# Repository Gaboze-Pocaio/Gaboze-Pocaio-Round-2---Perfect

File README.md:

-----

# Where Can I Buy One
> You can purchase an assembled Gaboze Pocaio - Round 2 on [Tindie](https://www.tindie.com/products/thirtytwoteeth/gaboze-pocaio-round-2/)

-----

# 
> This is it!

Based on the popularity of the original [Gaboze Pocaio](https://github.com/32teeth/GabozePocaio-Round1) and it's many updates. We have taken the *Gaboze Pocaio - Plus Edition* which featured the 2.6" TFT *(ILI9342)* and added a few more features

Project Code Name: ***'Play It Again'***

## Introduction
> Do we need one?

### Features
> Things you can find on this kit

- 2.6" TFT LCD
- USB peripheral support for *3.3v accessories* (ie: keyboards)
- Brightness Control Thumbwheel
- Volume Control Thumbwheel
- Power LED - 3mm diffused
- New Conductive Pads
- Through Hole Raspberry Pi Zero Mounting Header
- Battery Charger (TP4056 Module)
- Headphone Jack (LM4857)
- Speaker capability (LM4857)
- Audio Amp (LM4857)

| Top Side Features | Bottom Side Features |
| - | - |
|  |  |

### Platform Support:

- [x] [Emulation Station](http://www.emulationstation.org/)
- [x] [Lakka](http://www.lakka.tv/)
- [x] [RetroPie](https://retropie.org.uk/)

*For [Lakka](http://www.lakka.tv/) implementation you can follow the ['paint by numbers' tutorial](https://github.com/32teeth/Lakka-For-Gaboze-Pocaio)*

#### New Feature Discussion
> A little more behind the features

##### TFT
> A new screen

An adoption from the *Gaboze Pocaio - Plus Edition*. The screen is now a 2.6" TFT, which fills the screen area of the Game Boy Pocket shell much better. No more resizing of the video driver output!

##### Brightness Control
> Mechanical Adjustment FTW

Although there are many implementations of *software* based screen brightness adjustment. This model features a **thubwheel**, which means you don't need to worry about knowing how, or where to put the *software* based controls.

This also allows for using different *Operating Systems* and having brightness control out of the box

##### Through Hole Header
> No more loose connections

With the new Raspberry Pi Zero mounting system using a through hole header, you will no longer loosen the pin connection if using an unregulated (non temperature) control soldering iron...   ...yay

The short insulation on the header also means you can mount the Raspberry Pi flat against the headers

##### New Conductive Pads
> Better response. Simply put

With a redesigned conductive pad, you can now have a better response rate to your silicon aftermarket pads.

##### USB peripheral support
> No connection? No Problem

This is a 3.3V USB peripheral support, like keyboards (not the LED mechanical ones), older joysticks / gamepads *(can you say retro pads!)*

One of the most requested features is to be able to use your keyboard and terminal without having to connect to the network, SSH, SCP, or FTP.

##### Power LED
> Domed and diffused

We replaced the surface mount power indicator LED with a through hole domed and diffused 3mm LED. This fits perfectly in the LED hole of the original and aftermarket *Game Boy Pocket* shell

## What you need
> Batteries not included

In order to complete your build. You will need:

- Raspberry Pi Zero W
- LiPo Battery
- Micro SD Card
- Gameboy Pocket Shell

## Releases
> Retro Pie or Lakka - You Decide

* [Retro Pie](https://github.com/32teeth/GabozePocaio-Round2/releases/tag/RetroPie)
* [Lakka](https://github.com/32teeth/GabozePocaio-Round2/releases/tag/Lakka)

### Direct Downloads

#### Retro Pie
* [IMG](http://gameboy.32teeth.org/Gaboze-Round2-RetroPie.img)
* [GZIP](http://gameboy.32teeth.org/Gaboze-Round2-RetroPie.gz)

#### Lakka
* [IMG](http://gameboy.32teeth.org/Gaboze-Round2-Lakka.img)
* [GZIP](http://gameboy.32teeth.org/Gaboze-Round2-Lakka.gz)

### Get In Touch

|      |
| ---- |
| Find us on the internet and lets chat |

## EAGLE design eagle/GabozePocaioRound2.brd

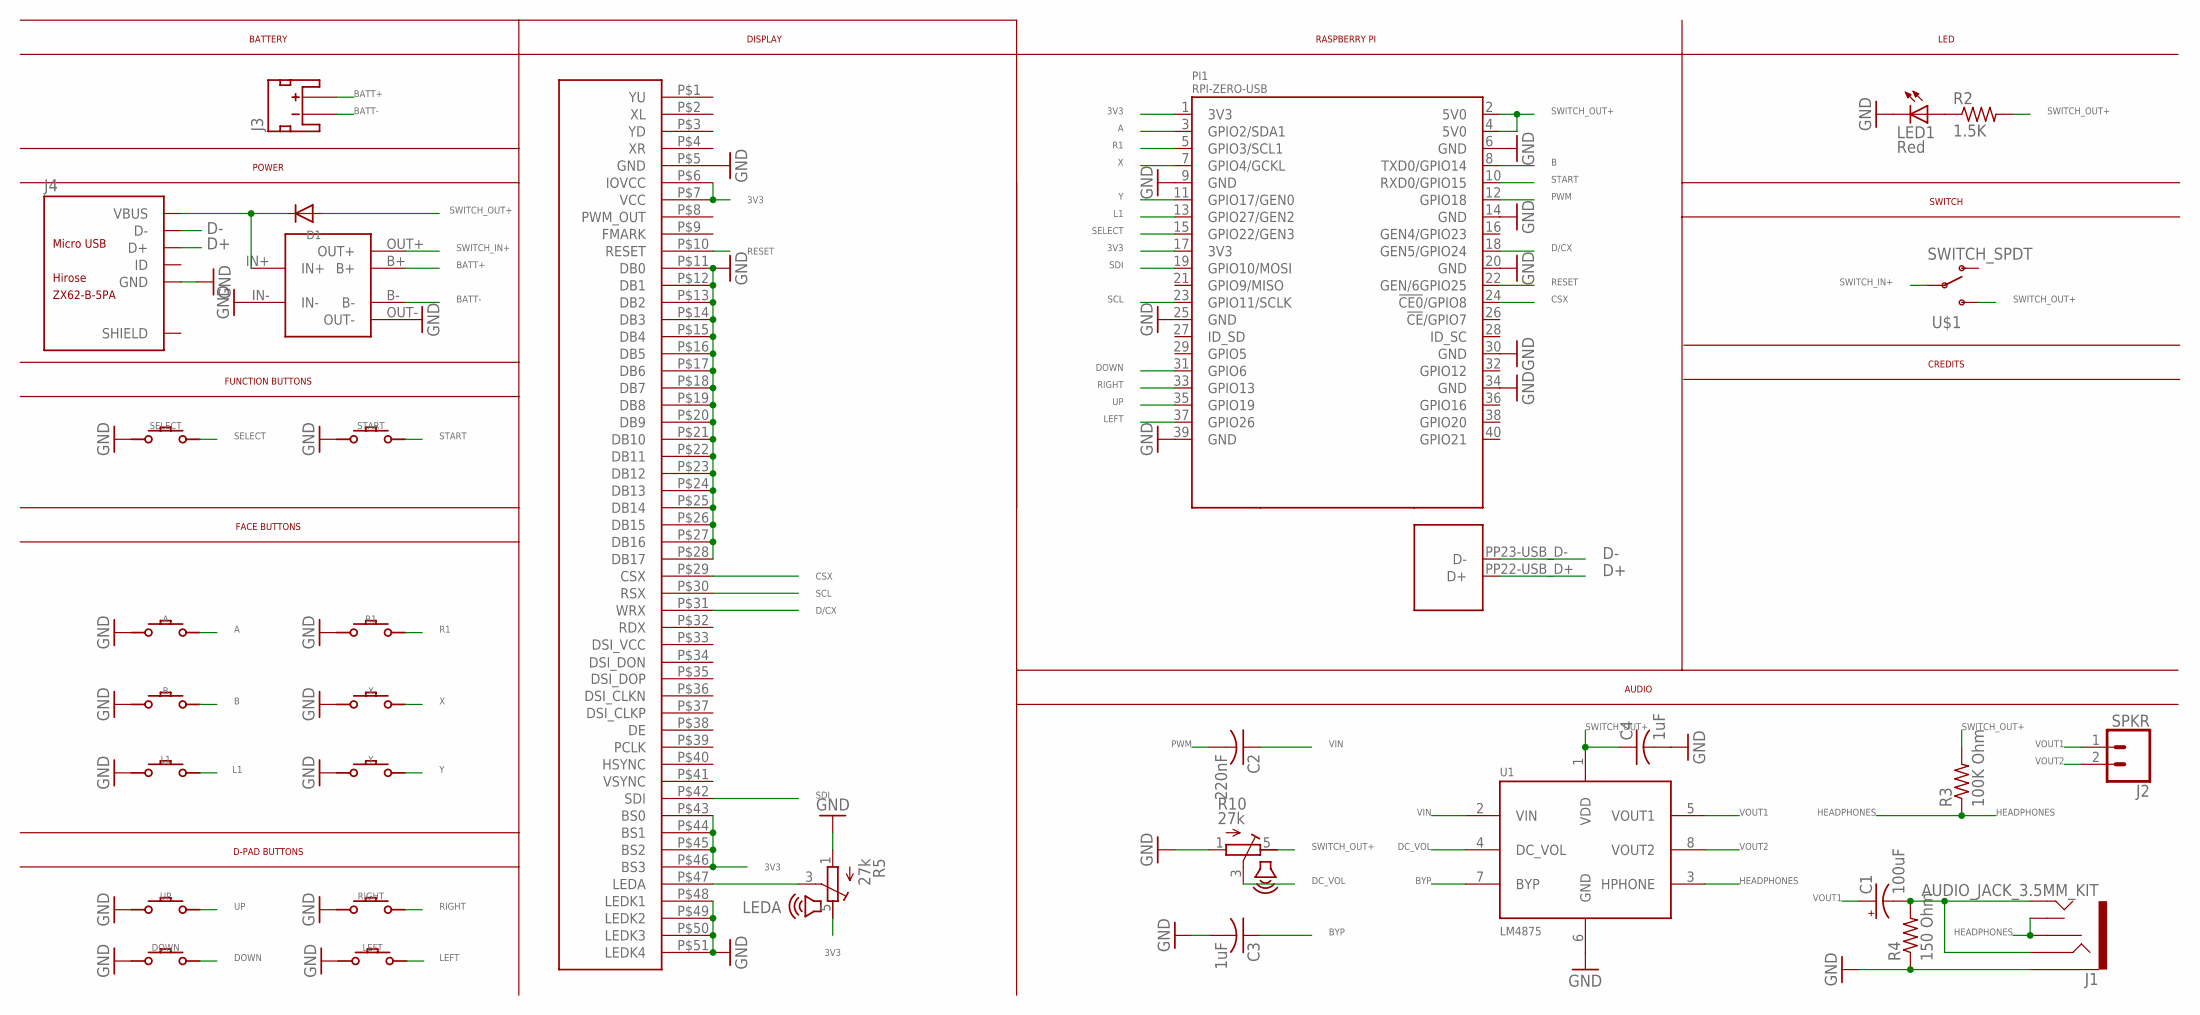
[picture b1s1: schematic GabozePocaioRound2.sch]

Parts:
A: CONDUCTIVE_BUTTONCONDUCTIVE_BUTTON_THICK; CONDUCTIVE_BUTTON_THICK
B: CONDUCTIVE_BUTTONCONDUCTIVE_BUTTON_THICK; CONDUCTIVE_BUTTON_THICK
C1: 100uF; EIA3216
C2: 220nF; C0805
C3, C4: 1uF; C0805
D1: DIODE_SOD-123FL; SOD-123FL
DOWN: CONDUCTIVE_BUTTONCONDUCTIVE_BUTTON_DIRECTIONAL_TH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; CONDUCTIVE_BUTTON_DIRECTIONAL_THICK
J1: AUDIO_JACK_3.5MM_KIT; AUDIO-JACK-KIT
J2: SPKR; 1X02
J3: Batt Conn; JST-2-SMD
J4: ZX62-B-5PA; MICRO-USB5+6P-SMD-0.65-AB
L1: CONDUCTIVE_BUTTON_DRILLCONDUCTIVE_BUTTON_DRILL_TH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; CONDUCTIVE_BUTTON_THICK_DRILL
LED1: Red; LED3MM
LEFT: CONDUCTIVE_BUTTONCONDUCTIVE_BUTTON_DIRECTIONAL_TH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; CONDUCTIVE_BUTTON_DIRECTIONAL_THICK
PI1: RPI-ZERO-USB; RPI-ZERO-TH-USB-POGO
POWER1: TP4056
R1: CONDUCTIVE_BUTTON_DRILLCONDUCTIVE_BUTTON_DRILL_TH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; CONDUCTIVE_BUTTON_THICK_DRILL
R2: 1.5K; R0805
R3: 100K Ohm; R0805
R4: 150 Ohm; R0805
R5, R10: 27k; VOLUME
RIGHT: CONDUCTIVE_BUTTONCONDUCTIVE_BUTTON_DIRECTIONAL_TH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; CONDUCTIVE_BUTTON_DIRECTIONAL_THICK
SELECT: CONDUCTIVE_BUTTON_STARTSELECTCONDUCTIVE_BUTTON_TH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; CONDUCTIVE_BUTTON_THICK_STARTSELECT
START: CONDUCTIVE_BUTTON_STARTSELECTCONDUCTIVE_BUTTON_TH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; CONDUCTIVE_BUTTON_THICK_STARTSELECT
U1: LM4875; SOIC8
U$1: SWITCH_SPDT; KPS-1290
U$2: TFT-DISPLAY-2.6-51PIN
UP: CONDUCTIVE_BUTTONCONDUCTIVE_BUTTON_DIRECTIONAL_TH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; CONDUCTIVE_BUTTON_DIRECTIONAL_THICK
X: CONDUCTIVE_BUTTON_DRILLCONDUCTIVE_BUTTON_DRILL_TH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; CONDUCTIVE_BUTTON_THICK_DRILL
Y: CONDUCTIVE_BUTTON_DRILLCONDUCTIVE_BUTTON_DRILL_TH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; CONDUCTIVE_BUTTON_THICK_DRILL

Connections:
3V3: PI1.1 (3V3), PI1.17 (3V3), R5.5 (E), U$2.P$6 (IOVCC), U$2.P$7 (VCC), U$2.P$43 (BS0), U$2.P$44 (BS1), U$2.P$45 (BS2), U$2.P$46 (BS3)
A: A.P$ACTIVE, PI1.3 (GPIO2/SDA1)
B: B.P$ACTIVE, PI1.8 (TXD0/GPIO14)
BATT+: J3.2 (+), POWER1.B+
BATT-: J3.1 (-), POWER1.B-
BYP: C3.1, U1.7 (BYP)
CSX: PI1.24 (!CE0!/GPIO8), U$2.P$29 (CSX)
D+: J4.3 (D+), PI1.PP22-USB_D+ (D+)
D-: J4.2 (D-), PI1.PP23-USB_D- (D-)
D/CX: PI1.18 (GEN5/GPIO24), U$2.P$31 (WRX)
DC_VOL: R10.3 (S), U1.4 (DC_VOL)
DOWN: DOWN.P$ACTIVE, PI1.31 (GPIO6)
GND: A.P$GND, B.P$GND, C3.2, C4.2, DOWN.P$GND, J1.SLEEVE, J4.5 (GND), L1.P$GND, LED1.K (C), LEFT.P$GND, PI1.6 (GND), PI1.9 (GND), PI1.14 (GND), PI1.20 (GND), PI1.25 (GND), PI1.30 (GND), PI1.34 (GND), PI1.39 (GND), POWER1.IN-, POWER1.OUT-, R1.P$GND, R4.1, R5.1 (A), R10.1 (A), RIGHT.P$GND, SELECT.P$GND, SELECT.P$GND1 (P$GND), SELECT.P$GND2 (P$GND), SELECT.P$GND3 (P$GND), START.P$GND, START.P$GND1 (P$GND), START.P$GND2 (P$GND), START.P$GND3 (P$GND), U1.6 (GND), U$2.P$5 (GND), U$2.P$11 (DB0), U$2.P$12 (DB1), U$2.P$13 (DB2), U$2.P$14 (DB3), U$2.P$15 (DB4), U$2.P$16 (DB5), U$2.P$17 (DB6), U$2.P$18 (DB7), U$2.P$19 (DB8), U$2.P$20 (DB9), U$2.P$21 (DB10), U$2.P$22 (DB11), U$2.P$23 (DB12), U$2.P$24 (DB13), U$2.P$25 (DB14), U$2.P$26 (DB15), U$2.P$27 (DB16), U$2.P$28 (DB17), U$2.P$48 (LEDK1), U$2.P$49 (LEDK2), U$2.P$50 (LEDK3), U$2.P$51 (LEDK4), UP.P$GND, X.P$GND, Y.P$GND
HEADPHONES: J1.RSH, J1.TSH, R3.1, U1.3 (HPHONE)
L1: L1.P$ACTIVE, PI1.13 (GPIO27/GEN2)
LED: LED1.A, R2.1
LEDA: R5.3 (S), U$2.P$47 (LEDA)
LEFT: LEFT.P$ACTIVE, PI1.37 (GPIO26)
PWM: C2.2, PI1.12 (GPIO18)
R1: PI1.5 (GPIO3/SCL1), R1.P$ACTIVE
RESET: PI1.22 (GEN/6GPIO25), U$2.P$10 (RESET)
RIGHT: PI1.33 (GPIO13), RIGHT.P$ACTIVE
SCL: PI1.23 (GPIO11/SCLK), U$2.P$30 (RSX)
SDI: PI1.19 (GPIO10/MOSI), U$2.P$42 (SDI)
SELECT: PI1.15 (GPIO22/GEN3), SELECT.P$ACTIVE, SELECT.P$ACTIVE1 (P$ACTIVE), SELECT.P$ACTIVE2 (P$ACTIVE), SELECT.P$ACTIVE3 (P$ACTIVE)
START: PI1.10 (RXD0/GPIO15), START.P$ACTIVE, START.P$ACTIVE1 (P$ACTIVE), START.P$ACTIVE2 (P$ACTIVE), START.P$ACTIVE3 (P$ACTIVE)
SWITCH_IN+: POWER1.OUT+, U$1.P
SWITCH_OUT+: C4.1, D1.A, PI1.2 (5V0), PI1.4 (5V0), R2.2, R3.2, R10.5 (E), U1.1 (VDD), U$1.S
UP: PI1.35 (GPIO19), UP.P$ACTIVE
VIN: C2.1, U1.2 (VIN)
VIN1: C1.-, J1.RING, J1.TIP, R4.2
VOUT1: C1.+, J2.1, U1.5 (VOUT1)
VOUT2: J2.2, U1.8 (VOUT2)
VUSB: D1.C, J4.1 (VBUS), POWER1.IN+
X: PI1.7 (GPIO4/GCKL), X.P$ACTIVE
Y: PI1.11 (GPIO17/GEN0), Y.P$ACTIVE

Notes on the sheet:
D-PAD BUTTONS
FACE BUTTONS
FUNCTION BUTTONS
POWER
BATTERY
SWITCH
LED
DISPLAY
RASPBERRY PI
AUDIO
CREDITS

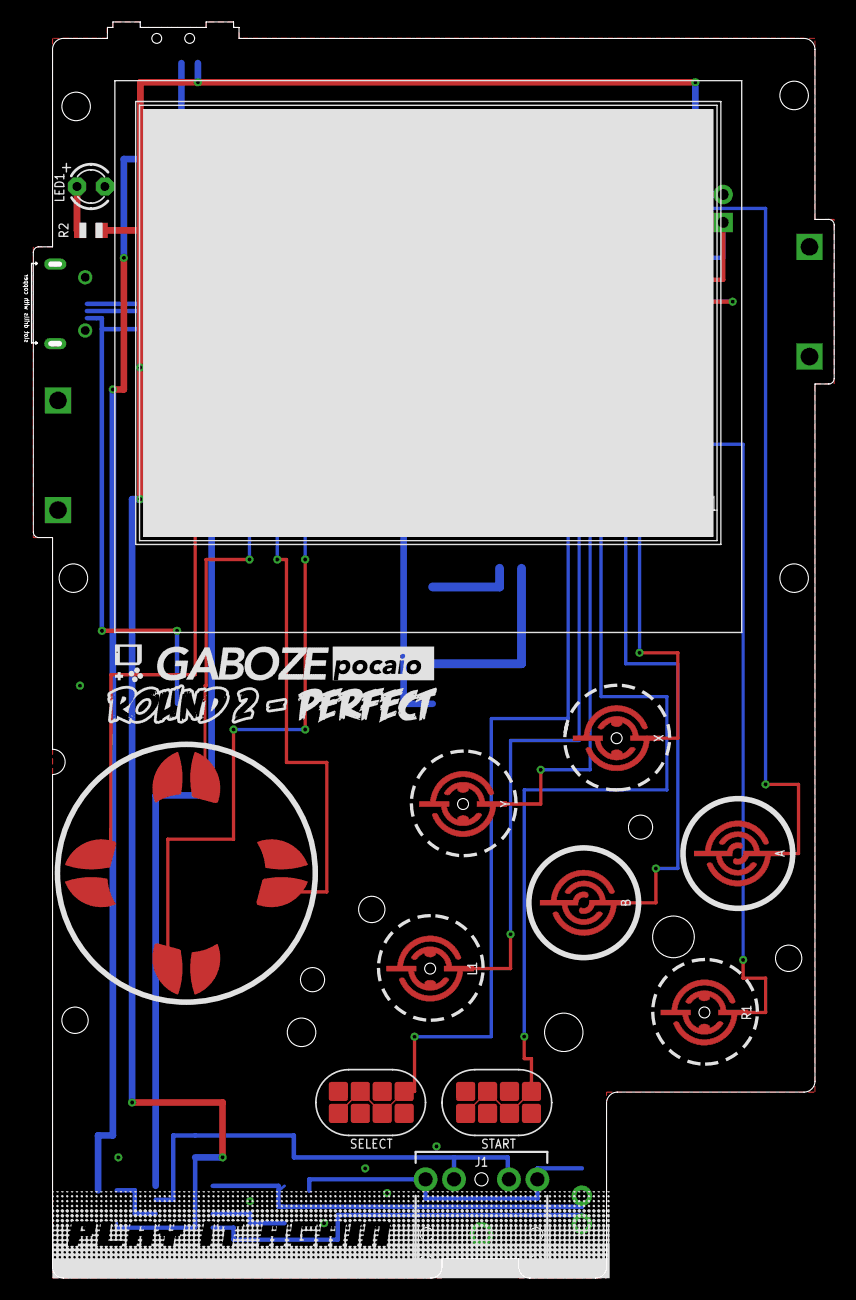
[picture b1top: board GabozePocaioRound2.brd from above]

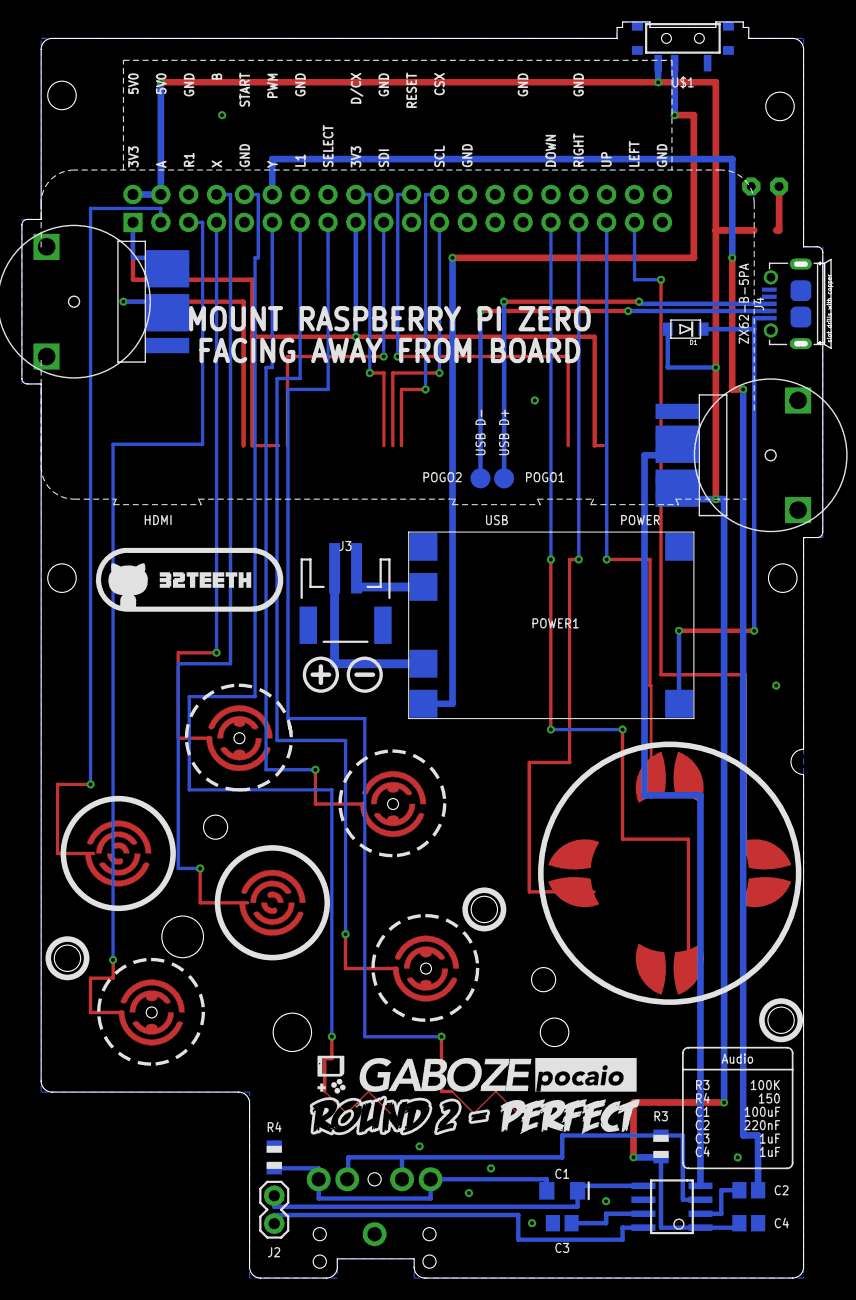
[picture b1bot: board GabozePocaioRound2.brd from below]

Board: 2 copper layers, 73.5 x 114.0 mm, 32 parts (16 on the bottom side), 36 nets.

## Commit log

2018-10-29 Mon 29 Oct 2018 13:51:11 EDT - Fork from dev to new repository
2018-10-29 Mon 29 Oct 2018 13:52:53 EDT - Fork from dev to new repository
2018-10-29 Mon 29 Oct 2018 13:53:19 EDT - Fork from dev to new repository
2018-10-29 Mon 29 Oct 2018 13:59:56 EDT - Fork from dev to new repository
2018-10-30 Tue 30 Oct 2018 15:43:02 EDT - Fork from dev to new repository
2018-10-30 Tue 30 Oct 2018 15:45:45 EDT - Fork from dev to new repository
2018-10-30 Tue 30 Oct 2018 16:08:03 EDT - Fork from dev to new repository
2018-10-30 Tue 30 Oct 2018 16:44:47 EDT - Fork from dev to new repository
2018-10-31 Wed 31 Oct 2018 14:22:59 EDT - pre flight license
2018-11-05 Mon 5 Nov 2018 08:24:36 EST - pre flight license
2018-11-05 Mon 5 Nov 2018 13:08:58 EST - pre flight license
2018-11-05 Mon 5 Nov 2018 13:57:00 EST
2018-11-06 Tue 6 Nov 2018 09:43:30 EST
2018-11-06 Tue 6 Nov 2018 16:08:26 EST
2018-11-06 Tue 6 Nov 2018 16:08:51 EST
2018-11-15 Thu 15 Nov 2018 06:35:52 EST - Links
2018-11-15 Thu 15 Nov 2018 06:36:45 EST - Links
2018-11-15 Thu 15 Nov 2018 06:38:50 EST - Links
2018-11-15 Thu 15 Nov 2018 06:39:15 EST - Releases
2018-11-15 Thu 15 Nov 2018 06:39:51 EST - Releases
2018-11-16 Fri 16 Nov 2018 18:18:55 EST - Assembly Tutuorial
2018-11-26 Mon 26 Nov 2018 11:53:58 EST - resotred images
2018-11-26 Mon 26 Nov 2018 11:55:31 EST - resotred images
2018-11-26 Update issue templates
2019-01-17 Thu 17 Jan 2019 10:50:48 EST - Happy Chinese New Year w/ Eagle and Gerber Release
2019-05-01 Wed 1 May 2019 12:41:43 EDT - changed thermals
2020-04-06 Correct the value of C2 to 220nF in Eagle and BOM files
    In the datasheet of LM4875 [1], Texas Instruments recommends
    a 0.22uF (which is 220nF [2]) AC-coupling capacitor at the
    audio input port [3]. However, in the Eagle and BOM files of
    Gaboze Pocaio Round 2, the capacitor value was specified
    as 220pF by accident. Experiments showed that using a 220pF
    capacitor instead of 220nF causes an audible distortion

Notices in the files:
parts and their libraries:
SparkFun-Connectors: Licensing: Creative Commons ShareAlike 4.0 International - https://creativecommons.org/licenses/by-sa/4.0
